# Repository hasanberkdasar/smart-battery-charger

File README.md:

# Smart Battery Charger

A KiCad 10 project for a PWM-controlled buck charging stage with voltage and current sensing. The repository contains the editable schematic and PCB layout.

> **Project status:** Hardware design / prototype. Battery chemistry, charging profile, input voltage range, output current, and controller firmware are not specified in this repository. Review and validate the complete system before connecting a battery.

## Design at a glance

| Block | Parts / signals | Purpose |
| --- | --- | --- |
| Power input | `J1` | Two-pin input terminal |
| Buck stage | `Q1` IRF7404, `L1` 33 µH, Schottky diodes | Switching power path |
| Current sensing | `R9` 0.02 Ω, `U1` LM358, `CURRENT_SENSE_ADC` | Current measurement signal |
| Voltage sensing | `VOLTAGE_SENSE_ADC` | Output voltage measurement signal |
| Control | `PWM_OUT`, `Q2` BC847 | PWM-driven switching control |
| Battery/output | `J2` | Two-pin output terminal |

The ADC and PWM names are **schematic labels**, not a documented external connector interface. In particular, KiCad reports that `PWM_OUT` is connected to only one schematic pin. Integrating a controller requires checking the actual PCB connections and adding a suitable physical interface as needed.

## Previews

### Schematic

### PCB front

## Open the project

1. Install [KiCad](https://www.kicad.org/) 10 or newer.
2. Open `Smartbattrycharger.kicad_pro` in KiCad Project Manager.
3. Open the schematic and PCB from the project window. Review footprints, component ratings, and design rules before fabrication.

## Repository files

- `Smartbattrycharger.kicad_pro` — KiCad project settings
- `Smartbattrycharger.kicad_sch` — editable schematic
- `Smartbattrycharger.kicad_pcb` — editable PCB layout
- `images/` — exported PNG previews and SVG source renders

## Design checks

Checked with **KiCad CLI 10.0.6**:

- PCB DRC: **0 violations, 0 unconnected items**.
- Schematic ERC: **1 warning** — `PWM_OUT` is an isolated pin label.

These automated checks do not establish electrical safety or suitability for a particular battery. Confirm the power supply, charging algorithm, thermal performance, and protection requirements for the intended use.

## License

This project is licensed under the [MIT License](LICENSE). Copyright (c) 2026 Hasan Berk Daşar.

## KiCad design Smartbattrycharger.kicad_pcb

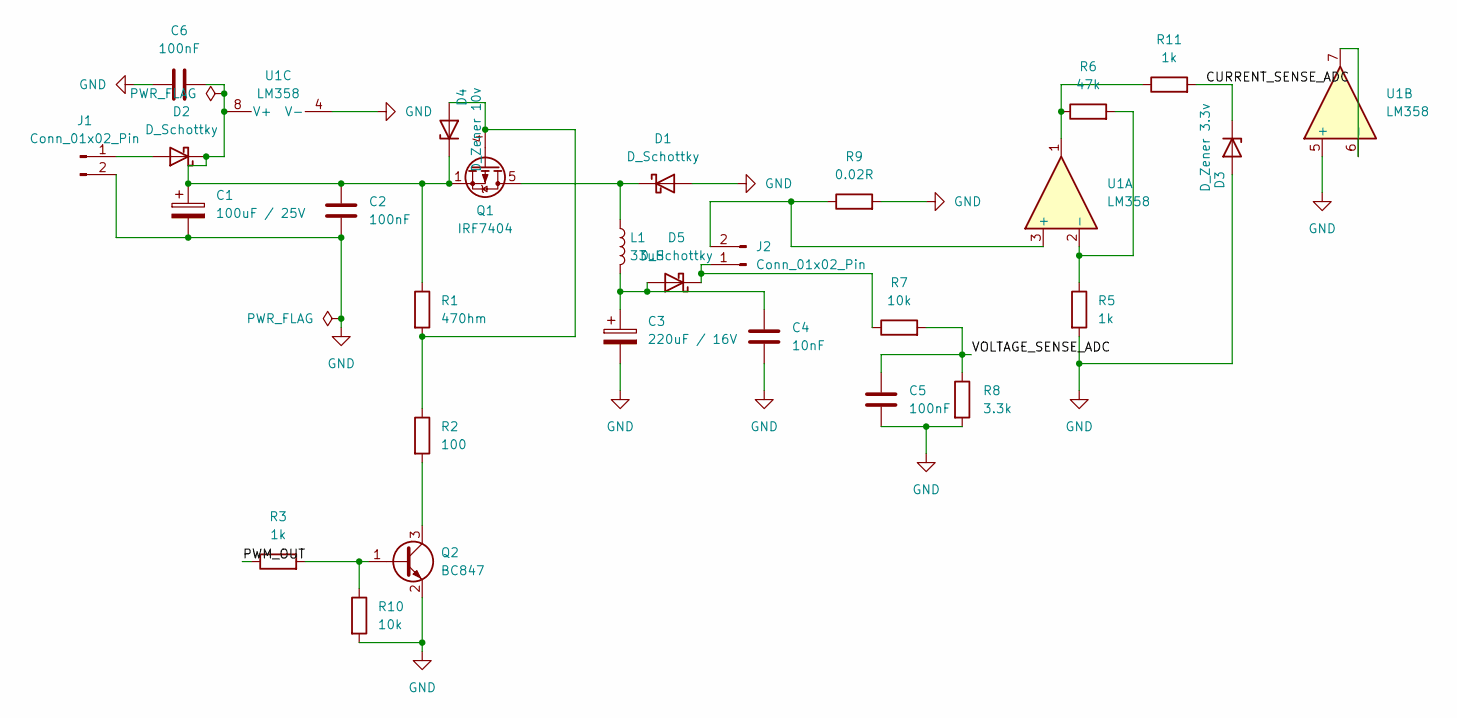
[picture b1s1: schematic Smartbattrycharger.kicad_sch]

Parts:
C1: 100uF / 25V; CP_Radial_D6.3mm_P2.50mm
C2, C5, C6: 100nF; C_1206_3216Metric_Pad1.33x1.80mm_HandSolder
C3: 220uF / 16V; CP_Radial_D6.3mm_P2.50mm
C4: 10nF; C_1206_3216Metric_Pad1.33x1.80mm_HandSolder
D1, D2, D5: D_Schottky; D_SMA
D3: D_Zener 3.3v; D_SOD-123
D4: D_Zener 10v; D_SOD-123
J1, J2: Conn_01x02_Pin; TerminalBlock_Phoenix_MKDS-1,5-2-5.08_1x02_P5.08mm_Horizont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
L1: 33uH; L_12x12mm_H6mm
Q1: IRF7404; SOIC-8_3.9x4.9mm_P1.27mm
Q2: BC847; SOT-23
R1: 470hm; R_1206_3216Metric
R2: 100; R_1206_3216Metric
R3, R5, R11: 1k; R_1206_3216Metric
R6: 47k; R_1206_3216Metric
R7, R10: 10k; R_1206_3216Metric
R8: 3.3k; R_1206_3216Metric
R9: 0.02R; R_1206_3216Metric
U1: LM358; SOIC-8_3.9x4.9mm_P1.27mm

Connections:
/CURRENT_SENSE_ADC: D3.1 (K), R11.2
/PWM_OUT: R3.1
/VOLTAGE_SENSE_ADC: C5.1, R7.2, R8.1
GND: C1.2, C2.2, C3.2, C4.2, C5.2, C6.1, D1.2 (A), D3.2 (A), J1.2, Q2.2 (E), R5.2, R8.2, R9.2, R10.2, U1.4 (V-), U1.5 (+)
unnamed: D1.1 (K), L1.1, Q1.5 (D), Q1.6 (D), Q1.7 (D), Q1.8 (D)
unnamed: D2.2 (A), J1.1
unnamed: C1.1, C2.1, C6.2, D2.1 (K), D4.1 (K), Q1.1 (S), Q1.2 (S), Q1.3 (S), R1.1, U1.8 (V+)
unnamed: D4.2 (A), Q1.4 (G), R1.2, R2.1
unnamed: C3.1, C4.1, D5.2 (A), L1.2
unnamed: D5.1 (K), J2.1, R7.1
unnamed: J2.2, R9.1, U1.3 (+)
unnamed: Q2.1 (B), R3.2, R10.1
unnamed: Q2.3 (C), R2.2
unnamed: R6.1, R11.1, U1.1
unnamed: R5.1, R6.2, U1.2 (-)
unnamed: U1.6 (-), U1.7

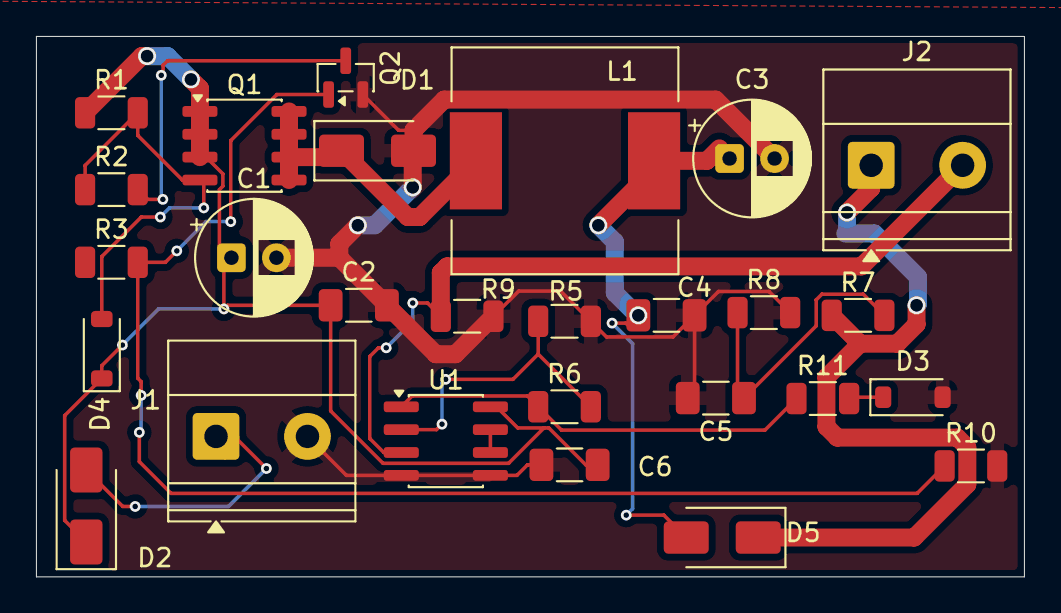
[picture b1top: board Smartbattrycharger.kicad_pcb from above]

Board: 2 copper layers, 54.9 x 30.0 mm, 27 parts (0 on the bottom side), 15 nets.
